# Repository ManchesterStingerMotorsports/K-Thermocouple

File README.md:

# Thermocouple

Board layout used as base to combine strain gauge V2 (Johnson Node Hats) to reduce number of mounts needed.

K-Type Brake Pad Rubbing Thermocouple
https://www.tc.co.uk/thermocouples/brake-disc-thermocouple.html

Thermocouple Precision Op-Amp (w/ Cold Junction Compensation)
https://www.ti.com/lit/ds/symlink/ina129-ep.pdf

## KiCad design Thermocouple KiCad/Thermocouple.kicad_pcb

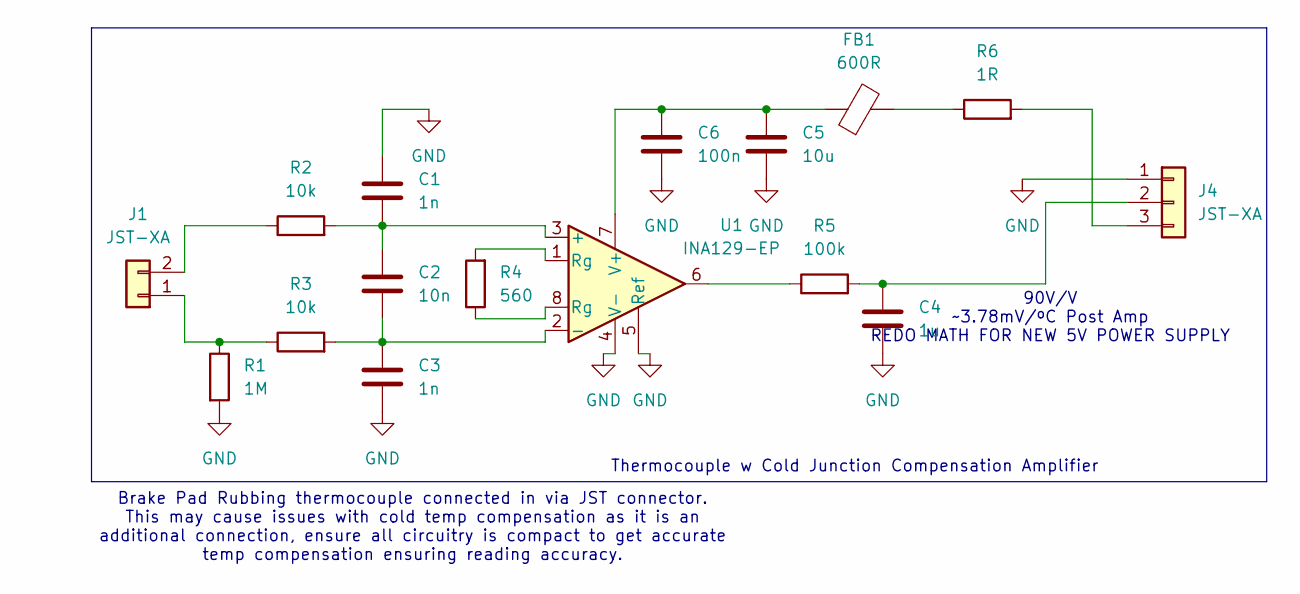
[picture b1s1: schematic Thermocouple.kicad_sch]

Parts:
C1, C3: 1n; C_0603_1608Metric
C2: 10n; C_0603_1608Metric
C4: 1u; C_0603_1608Metric
C5: 10u; C_0603_1608Metric
C6: 100n; C_0603_1608Metric
FB1: 600R; WE-CBF_0805_W4.0
J1: JST-XA; Connector_JST-XA_2POS
J4: JST-XA; Connector_JST-XA_3POS
R1: 1M; R_0603_1608Metric
R2, R3: 10k; R_0603_1608Metric
R4: 560; R_0603_1608Metric
R5: 100k; R_0603_1608Metric
R6: 1R; R_0603_1608Metric
U1: INA129-EP; Opamp_Dual_SOIC-8

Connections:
GND: C1.1, C3.2, C4.2, C5.2, C6.2, J4.1, R1.2, U1.4 (V-), U1.5 (Ref)
unnamed: FB1.2, R6.1
unnamed: J1.1, R1.1, R3.1
unnamed: J1.2, R2.1
unnamed: C4.1, J4.2, R5.2
unnamed: J4.3, R6.2
unnamed: R4.1, U1.8 (Rg)
unnamed: R4.2, U1.1 (Rg)
unnamed: R5.1, U1.6
unnamed: C1.2, C2.1, R2.2, U1.3 (+)
unnamed: C2.2, C3.1, R3.2, U1.2 (-)
unnamed: C5.1, C6.1, FB1.1, U1.7 (V+)

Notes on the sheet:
Thermocouple w Cold Junction Compensation Amplifier
Brake Pad Rubbing thermocouple connected in via JST connector. This may cause issues with cold temp compensation as it is an additional connection, ensure all circuitry is compact to get accurate temp compensation ensuring reading accuracy.
90V/V ~3.78mV/^{o}C Post Amp REDO MATH FOR NEW 5V POWER SUPPLY

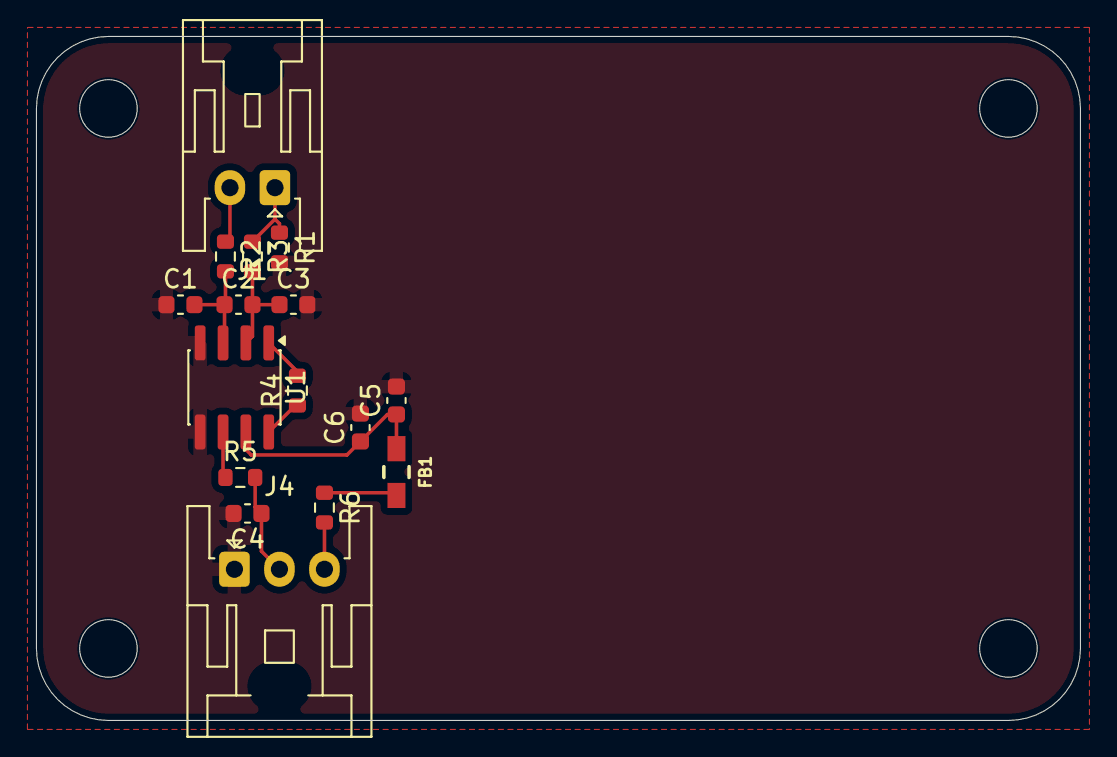
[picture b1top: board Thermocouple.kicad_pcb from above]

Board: 2 copper layers, 58.0 x 38.0 mm, 16 parts (0 on the bottom side), 12 nets.
